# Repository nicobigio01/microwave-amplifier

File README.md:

These are the main sources used in my bachelor thesis.

The sources are a little bit messy (latex ones in particular) but I was tight on time.

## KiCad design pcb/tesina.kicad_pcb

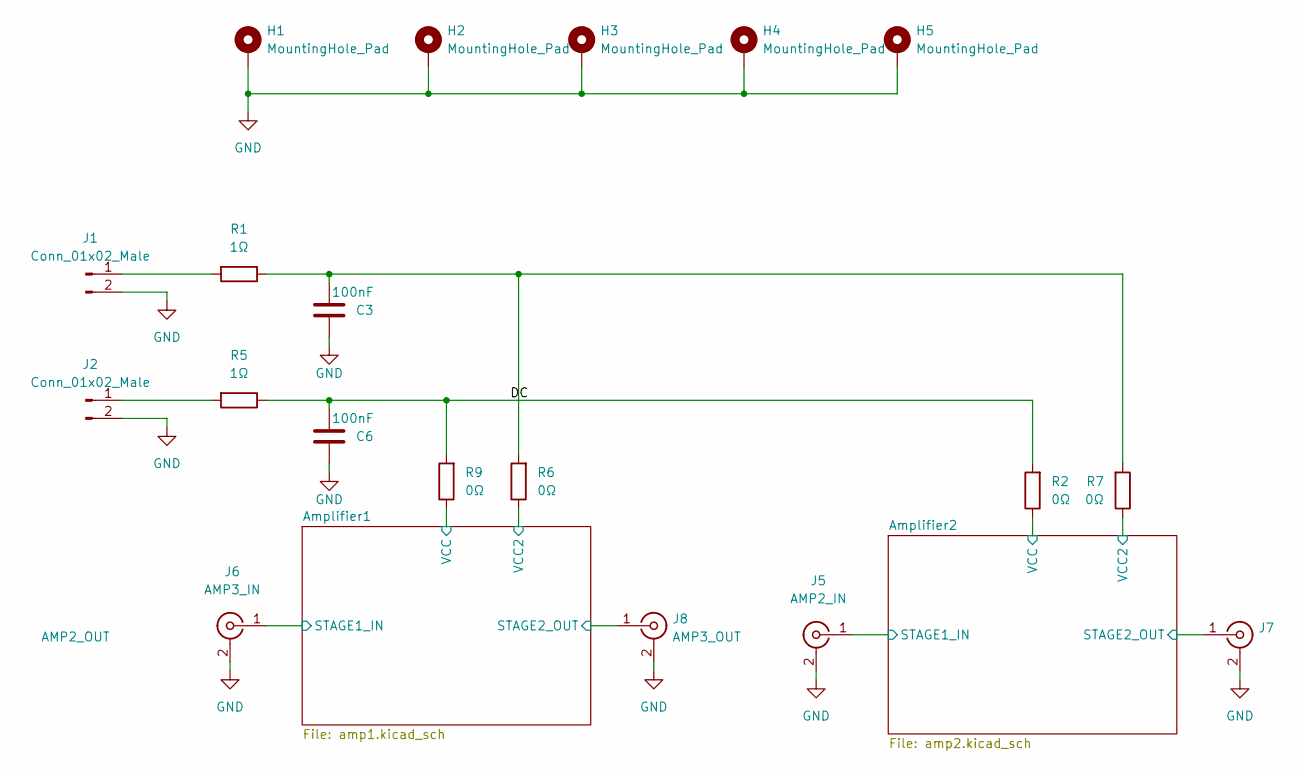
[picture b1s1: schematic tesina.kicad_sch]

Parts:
C3, C6: 100nF; C_1206_3216Metric
H1: MountingHole_Pad; MountingHole_2.5mm_Pad_TopBottom
H2, H3, H4, H5: MountingHole_Pad; MountingHole_2.7mm_M2.5_DIN965_Pad_TopBottom
J1, J2: Conn_01x02_Male; Connector_Pad
J5: AMP2_IN; Linx_CONSMA003.031-L-G
J6: AMP3_IN; Linx_CONSMA003.031-L-G
J7: AMP2_OUT; Linx_CONSMA003.031-L-G
J8: AMP3_OUT; Linx_CONSMA003.031-L-G
R1, R5: 1Ω; R_0603_1608Metric
R2, R6, R7, R9: 0Ω; R_0603_1608Metric

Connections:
/Amplifier1/STAGE1_IN: J6.1 (In); also elsewhere on the board
/Amplifier1/STAGE2_OUT: J8.1 (In); also elsewhere on the board
/Amplifier1/VCC: R9.1; also elsewhere on the board
/Amplifier1/VCC2: R6.1; also elsewhere on the board
/Amplifier2/STAGE1_IN: J5.1 (In); also elsewhere on the board
/Amplifier2/STAGE2_OUT: J7.1 (In); also elsewhere on the board
/Amplifier2/VCC: R2.1; also elsewhere on the board
/Amplifier2/VCC2: R7.1; also elsewhere on the board
/DC: C6.2, R2.2, R5.1, R9.2
GND: C3.1, C6.1, H1.1, H2.1, H3.1, H4.1, H5.1, J1.2, J2.2, J5.2 (Ext), J6.2 (Ext), J7.2 (Ext), J8.2 (Ext); also elsewhere on the board
unnamed: C3.2, R1.1, R6.2, R7.2
unnamed: J1.1, R1.2
unnamed: J2.1, R5.2

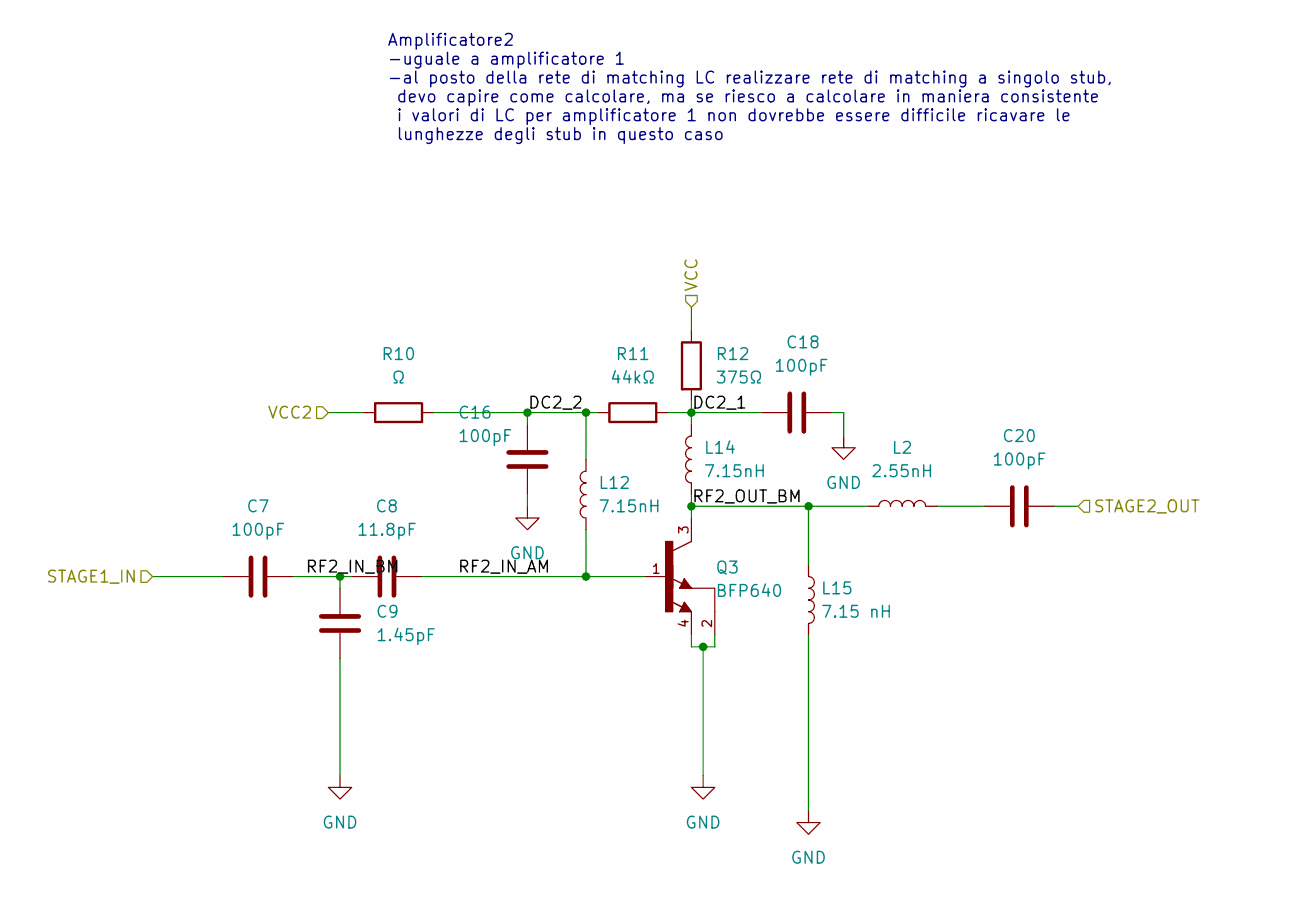
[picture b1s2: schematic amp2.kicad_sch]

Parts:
C7, C16, C18, C20: 100pF; C_0603_1608Metric
C8: 11.8pF; C_0603_1608Metric
C9: 1.45pF; C_0603_1608Metric
L2: 2.55nH; Coilcraft_0906-xxLx
L12, L14: 7.15nH; Coilcraft_1606-xxLx
L15: 7.15 nH; Coilcraft_mod
Q3: BFP640; SOT-343
R10: Ω; R_0603_1608Metric
R11: 44kΩ; R_0603_1608Metric
R12: 375Ω; R_0603_1608Metric

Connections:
/Amplifier2/DC2_1: C18.1, L14.2, R11.2, R12.2
/Amplifier2/DC2_2: C16.1, L12.2, R10.2, R11.1
/Amplifier2/RF2_IN_AM: C8.2, L12.1, Q3.1
/Amplifier2/RF2_IN_BM: C7.2, C8.1, C9.1
/Amplifier2/RF2_OUT_BM: L2.1, L14.1, L15.1, Q3.3
/Amplifier2/STAGE1_IN: C7.1; also elsewhere on the board
/Amplifier2/STAGE2_OUT: C20.2; also elsewhere on the board
/Amplifier2/VCC: R12.1; also elsewhere on the board
/Amplifier2/VCC2: R10.1; also elsewhere on the board
GND: C9.2, C16.2, C18.2, L15.2, Q3.2, Q3.4; also elsewhere on the board
unnamed: C20.1, L2.2

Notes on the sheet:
Amplificatore2 -uguale a amplificatore 1 -al posto della rete di matching LC realizzare rete di matching a singolo stub, devo capire come calcolare, ma se riesco a calcolare in maniera consistente i valori di LC per amplificatore 1 non dovrebbe essere difficile ricavare le lunghezze degli stub in q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

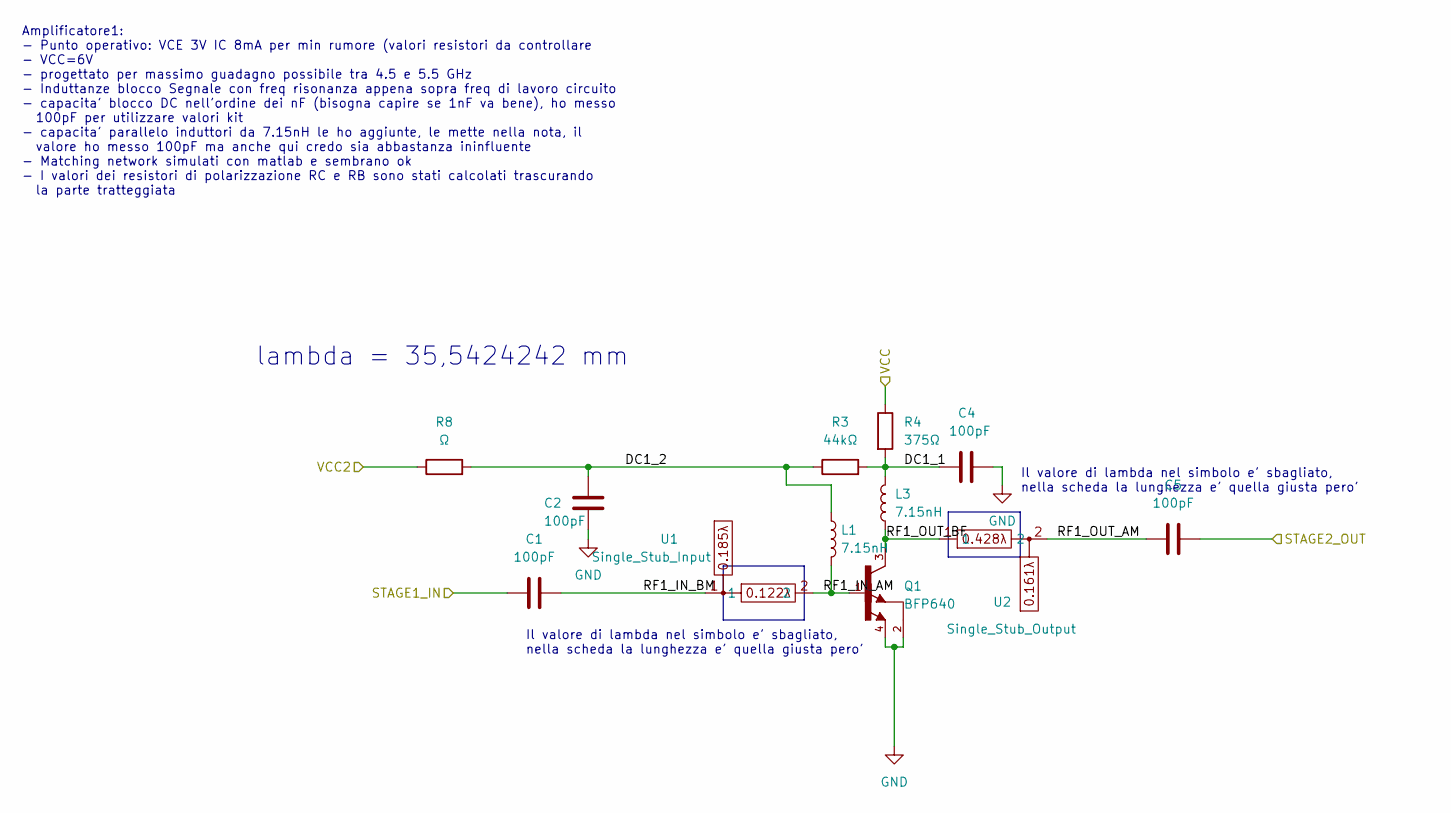
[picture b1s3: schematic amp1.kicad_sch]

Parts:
C1, C2, C4, C5: 100pF; C_0603_1608Metric
L1, L3: 7.15nH; Coilcraft_1606-xxLx
Q1: BFP640; SOT-343
R3: 44kΩ; R_0603_1608Metric
R4: 375Ω; R_0603_1608Metric
R8: Ω; R_0603_1608Metric
U1: Single_Stub_Input; Microwave_Stub_In2
U2: Single_Stub_Output; Microwave_Stub_Out2

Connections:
/Amplifier1/DC1_1: C4.1, L3.2, R3.2, R4.2
/Amplifier1/DC1_2: C2.1, L1.1, R3.1, R8.2
/Amplifier1/RF1_IN_AM: L1.2, Q1.1, U1.2
/Amplifier1/RF1_IN_BM: C1.2, U1.1
/Amplifier1/RF1_OUT_AM: C5.1, U2.2
/Amplifier1/RF1_OUT_BF: L3.1, Q1.3, U2.1
/Amplifier1/STAGE1_IN: C1.1; also elsewhere on the board
/Amplifier1/STAGE2_OUT: C5.2; also elsewhere on the board
/Amplifier1/VCC: R4.1; also elsewhere on the board
/Amplifier1/VCC2: R8.1; also elsewhere on the board
GND: C2.2, C4.2, Q1.2, Q1.4; also elsewhere on the board

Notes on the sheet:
Amplificatore1: - Punto operativo: VCE 3V IC 8mA per min rumore (valori resistori da controllare - VCC=6V - progettato per massimo guadagno possibile tra 4.5 e 5.5 GHz - Induttanze blocco Segnale con freq risonanza appena sopra freq di lavoro circuito - capacita' blocco DC nell'ordine dei nF (bisog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
lambda = 35,5424242 mm
Il valore di lambda nel simbolo e' sbagliato, nella scheda la lunghezza e' quella giusta pero'

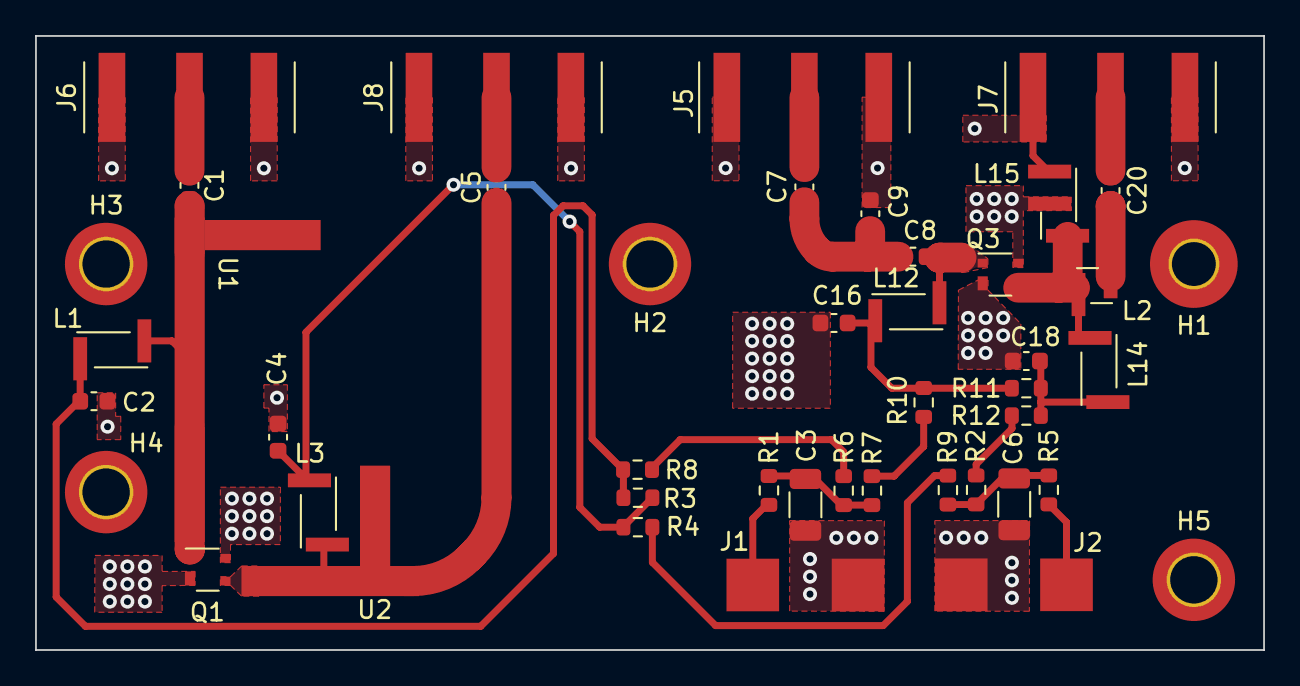
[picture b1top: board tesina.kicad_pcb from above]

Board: 2 copper layers, 70.0 x 35.0 mm, 45 parts (0 on the bottom side), 25 nets.

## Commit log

2023-04-01 started working on schematic
2023-04-01 Added values for matching network
2023-04-01 Added DC op. point analysis
2023-04-13 Created LTSpice simulation and added suggested fix
2023-04-27 Started working on board
2023-04-27 Schematic modified as discussed
2023-05-11 Deleted double stage, updated stub stage, L stage and PCB
2023-05-13 Started PCB Layout
2023-05-15 backup version before changes
2023-05-15 PCB modified according to suggestions
2023-05-15 alternate board
2023-05-16 design finished
2023-05-18 PCB ready for review
2023-06-19 cleanup
2023-06-28 started writing
2023-06-28 first s-par data
2023-06-28 new scripts
2023-06-28 misc
2023-06-28 draft finished
2023-06-29 matlab/BFP640
    L matching VCE 2V IC 40mA
2023-06-29 Added corrections
2023-07-01 preliminary part of -punto di lavoro- done
2023-07-02 preliminary part of -stabilita'- done
2023-07-03 saving last version before changes
2023-07-03 gain 22dB @ 1.6GHz
2023-07-03 Gain 14dB @ 1.6GHz
2023-07-06 Final version summary
2023-07-06 All data collected working on thesis
2023-07-12 Almost finished
2023-07-12 semi-final version
2023-07-20 graduated
2023-07-20 added readme
